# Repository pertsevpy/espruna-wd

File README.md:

# espruna-wd
Remix [espurna-h PCB](https://github.com/xoseperez/espurna-board)

I didn't need current metering HLW8012, however needed an increase in reliability.

I used the [xoseperez](https://github.com/xoseperez) design to make the board using the Watch Dog hardware.

Changes:
- Added hardware Watch Dog timer circuit STMicroelectronics STWD100. It is possible to use pin-to-pin analogs. Pin Enable has 2 pull-up options. Enabled by a jumper.
- 3mm mounting holes (Little space, but dimensions are preserved).
- Slightly changed the layout of the board, redrawn all the tracks of the PCB.
- More GPIOs brought out.

# Watchdog Notes:
- Please use the jumper (pin enable) to disable WD while flashing and configuring the device. Otherwise, you will get flickering.
- Please use STWD100xY (eg WNY marking) with a timeout period of 1.6s (1.12 - 2.24s). Otherwise, the ESP8266 may not boot up in time and you will get flickering.

## Open Hardware

Hardware designs (schematics and CAD) files are licensed under the [Creative Commons Attribution-ShareAlike 3.0 Unported License](http://creativecommons.org/licenses/by-sa/3.0/) and follow the terms of the [OSHW (Open-source hardware) Statement of Principles 1.0.](http://freedomdefined.org/OSHW)

## Disclaimer

THIS PRODUCT IS TARGETED TO EXPERIENCED USERS AT THEIR OWN RISK. THIS PRODUCT IS MEANT TO BE USED PLUGGED TO MAINS AND IT REQUIRES A DEEP UNDERSTANDING OF THE PERILS OF HIGH VOLTAGE ON HUMAN LIFE.

TO THE FULLEST EXTENT PERMISSIBLE BY THE APPLICABLE LAW, I HEREBY DISCLAIM ANY AND ALL RESPONSIBILITY, RISK, LIABILITY AND DAMAGES ARISING OUT OF DEATH OR PERSONAL INJURY RESULTING FROM ASSEMBLY OR OPERATION OF THIS PRODUCT.

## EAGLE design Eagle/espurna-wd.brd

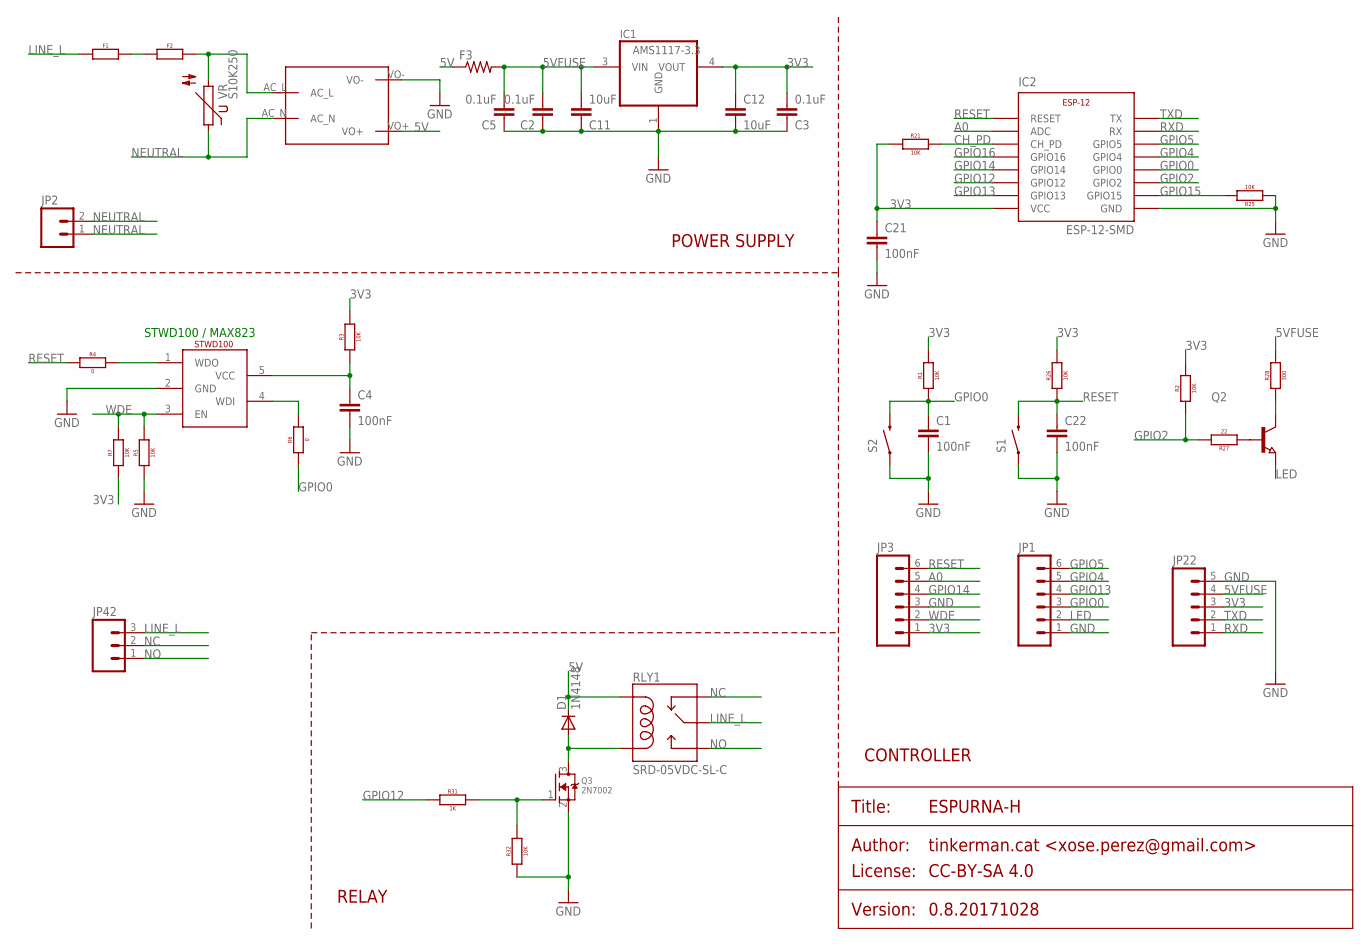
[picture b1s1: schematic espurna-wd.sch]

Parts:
C1, C4, C21, C22: 100nF; 0805
C2: 0.1uF; C1206K
C3, C5: 0.1uF; 0805
C11: 10uF; C1206K
C12: 10uF; C1206
D1: 1N4148; DO214BA
F1, F2: THERMALFUSE0.4; AXIAL-0.4
F3: RESISTOR1206; 1206
IC1: AMS1117-3.3; SOT223
IC2: ESP-12-SMD
JP1, JP3: M06NO_SILK_FEMALE_PTH; 1X06_NO_SILK
JP2: M02200MIL; SCREWTERMINAL-200MIL-2
JP22: M05PTH; 1X05
JP42: M03200MIL; SCREWTERMINAL-200MIL-3
Q2: NPN-TRANSISTOR_SOT23; SOT23
Q3: 2N7002; SOT23
R1, R2, R3, R5, R7, R21, R25, R26, R32: 10K; 0805
R4, R6: 0; 0805
R27: 22; 0805
R28: 300; 0805
R31: 1K; 0805
RLY1: SRD-05VDC-SL-C; SRD-5VDC-SL-C
S1, S2: SWITCH-MOMENTARY-2SMD-1101NE; TACTILE-SWITCH-1101NE
U$1: MAINS_CONVERTERS; HLK-PM01
VR: S10K250
WD: STWD100; SOT95P280X145-5N

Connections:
3V3: C3.2, C12.1, C21.1, IC1.4 (VOUT), IC2.VCC, JP3.1, JP22.3, R1.2, R2.2, R3.2, R7.1, R21.1, R26.2
5V: D1.C, F3.1, RLY1.COIL1, U$1.VO+
5VFUSE: C2.2, C5.2, C11.2, F3.2, IC1.3 (VIN), JP22.4, R28.2
A0: IC2.ADC, JP3.5
CH_PD: IC2.CH_PD, R21.2
GND: C1.2, C2.1, C3.1, C4.2, C5.1, C11.1, C12.2, C21.2, C22.2, IC1.1 (GND), IC2.GND, JP1.1, JP3.3, JP22.5, Q3.2 (S), R5.1, R25.1, R32.1, S1.1, S2.1, U$1.VO-, WD.2 (GND)
GPIO0: C1.1, IC2.GPIO0, JP1.3, R1.1, R6.1, S2.2
GPIO2: IC2.GPIO2, R2.1, R27.2
GPIO4: IC2.GPIO4, JP1.5
GPIO5: IC2.GPIO5, JP1.6
GPIO12: IC2.GPIO12, R31.1
GPIO13: IC2.GPIO13, JP1.4
GPIO14: IC2.GPIO14, JP3.4
GPIO15: IC2.GPIO15, R25.2
GPIO16: IC2.GPIO16
LED: JP1.2, Q2.2 (E)
LINE_L: F1.P$1 (1), JP42.3, RLY1.COMMON (MAIN)
LINE_P: F2.P$2 (2), U$1.AC_L, VR.2
unnamed: Q2.3 (C), R28.1
unnamed: Q2.1 (B), R27.1
unnamed: D1.A, Q3.3 (D), RLY1.COIL2
unnamed: Q3.1 (G), R31.2, R32.2
unnamed: C4.1, R3.1, WD.5 (VCC)
unnamed: F1.P$2 (2), F2.P$1 (1)
unnamed: R4.2, WD.1 (WDO)
unnamed: R6.2, WD.4 (WDI)
NC: JP42.2, RLY1.CLOSED (NC)
NEUTRAL: JP2.1, JP2.2, U$1.AC_N, VR.1
NO: JP42.1, RLY1.OPEN (NO)
RESET: C22.1, IC2.RESET, JP3.6, R4.1, R26.1, S1.2
RXD: IC2.RX, JP22.1
TXD: IC2.TX, JP22.2
WDE: JP3.2, R5.2, R7.2, WD.3 (EN)

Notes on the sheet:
POWER SUPPLY
RELAY
CONTROLLER
STWD100 / MAX823

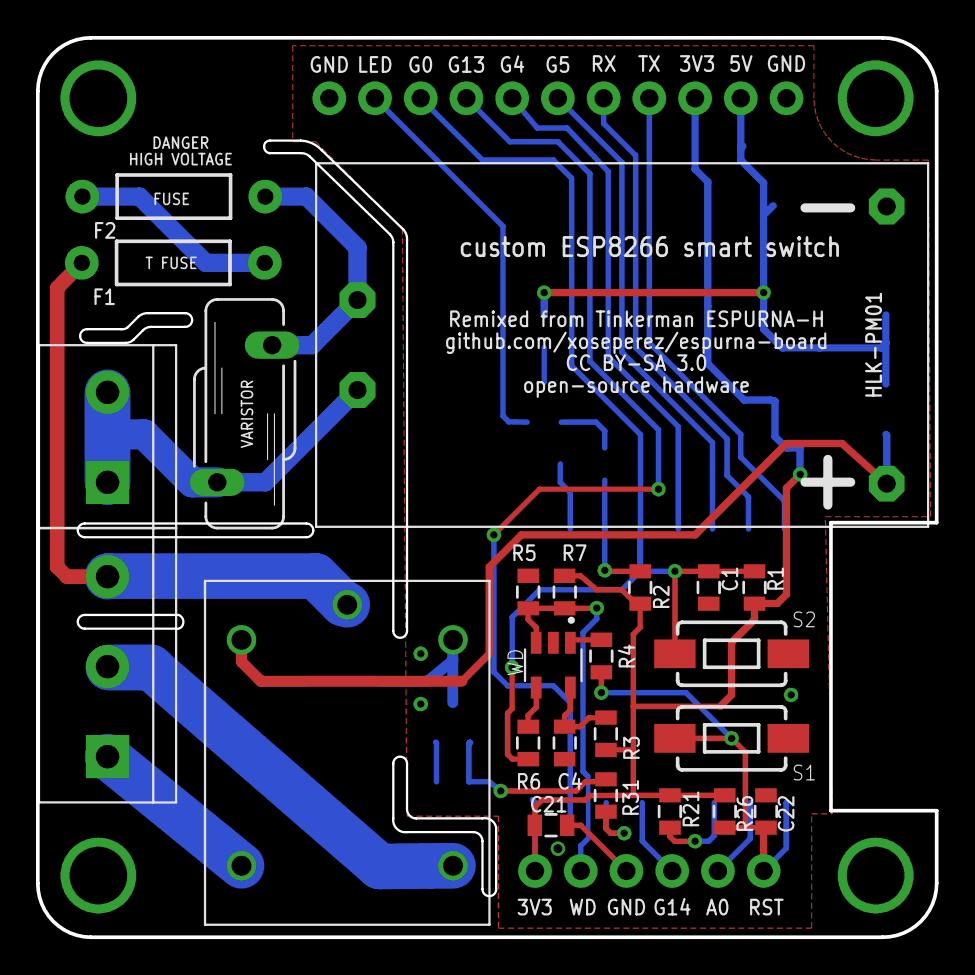
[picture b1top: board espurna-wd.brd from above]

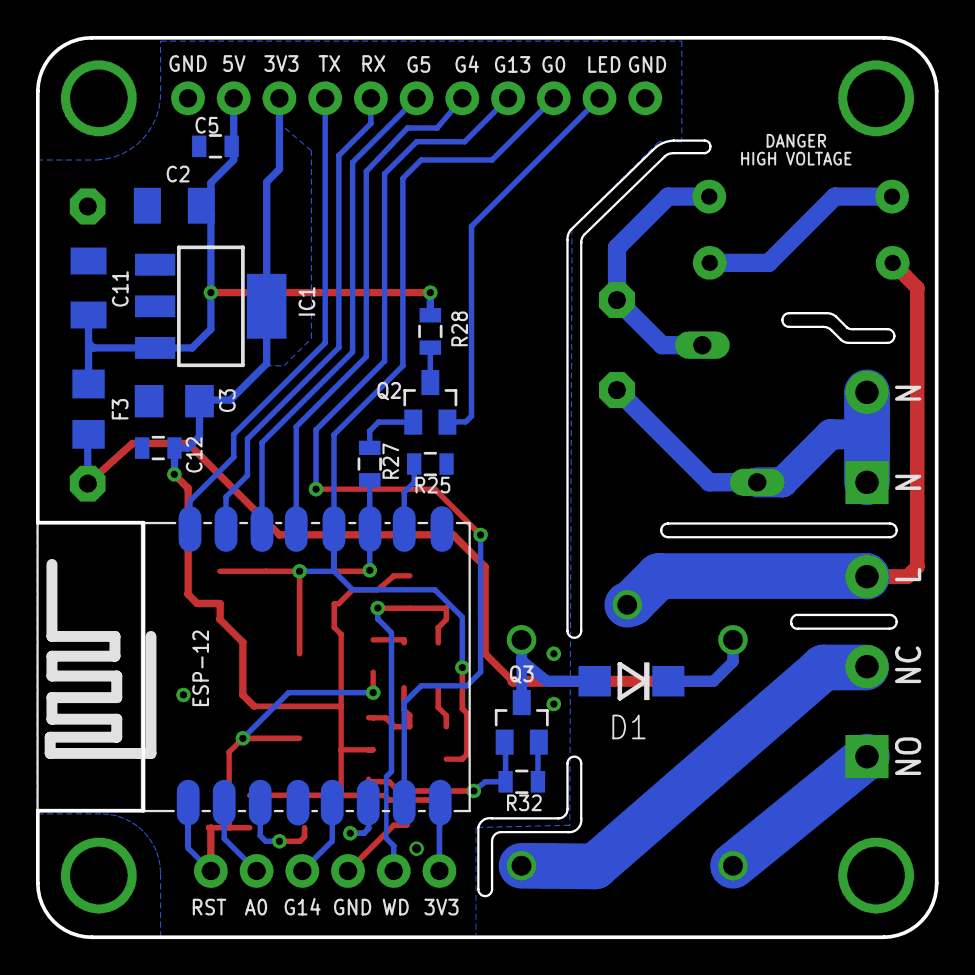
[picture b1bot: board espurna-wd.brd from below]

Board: 2 copper layers, 49.9 x 50.0 mm, 42 parts (15 on the bottom side), 32 nets.

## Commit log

2021-03-02 add PCB
2021-03-04 Change dir
2021-03-04 Add Gerber and CAM
2021-03-06 Add stl models
2021-03-13 tmp file
    some renaming and ordering
2021-03-13 TMP files
    some renaming and ordering
2021-03-16 added photos
2021-03-16 edit photo
2021-05-09 Add DIN mount STL
2021-05-12 Update wall_socket_cover.stl
    small changes
2022-12-08 Add files via upload
    https://www.st.com/resource/en/datasheet/stwd100.pdf

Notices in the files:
Eagle/espurna-wd.brd:
CC BY-SA 3.0
Eagle/espurna-wd.sch:
PROJECT_LICENSE: CC-BY-SA 4.0
parts and their libraries:
SparkFun-Connectors: Licensing: Creative Commons ShareAlike 4.0 International - https://creativecommons.org/licenses/by-sa/4.0
